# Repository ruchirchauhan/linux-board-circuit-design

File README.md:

# Custom SAM9X60 Embedded Linux Development Board

A custom-designed embedded development board based on the **Microchip SAM9X60** ARM926EJ-S microprocessor, designed to explore embedded Linux, hardware design, and low-level software development.

The project started with the goal of designing a minimal, fully functional Linux-capable board using the SAM9X60, taking inspiration from Microchip's SAM9X60 Curiosity evaluation board.

## Software Repository

The Operating System and board-bringup related documentation are maintained separately:

**[Linux Board OS](https://github.com/ruchirchauhan/linux-board-os)**

## Board Images

### 3D PCB Render

### Actual PCB

## Hardware Overview

| Component | Description |
|---|---|
| Processor | Microchip SAM9X60D1G-I/4FB |
| Power Management | Microchip MCP16501 PMIC |
| Ethernet PHY | Microchip KSZ8081RNAIA-TR |
| Ethernet Interface | 10/100 Mbps RMII |
| Storage | MicroSD card |
| Debug Interface | UART via USB-to-serial adapter |
| Power Input | 5V USB |

## Software Repository

The corresponding software repository contains the bootloader, Linux kernel configuration, device tree, and Buildroot configuration used to bring up and run embedded Linux on this board.

TODO
<!-- TODO **Software repository:** [SAM9X60 Linux Software](https://github.com/TODO) -->

## Software

The board has been successfully brought up with:

- U-Boot bootloader
- Microchip Linux4SAM kernel
- Buildroot-based embedded Linux filesystem

## Current Status

**Hardware bring-up completed successfully.**

All onboard peripherals are operational, including:

- Ethernet connectivity
- UART console
- MicroSD storage
- USB interfaces

The board successfully boots embedded Linux from microSD and provides a functional platform for further embedded software development and experimentation.

## Repository Contents

This repository contains the hardware design files for the custom SAM9X60 development board, including PCB layout and associated design resources.

## Project Goals

- Explore custom embedded hardware design.
- Gain hands-on experience with ARM-based embedded Linux platforms.
- Experiment with bootloaders, Linux kernel configuration, and device drivers.
- Develop and test embedded applications on custom hardware.

## Acknowledgments

The hardware design was developed with reference to Microchip's SAM9X60 Curiosity evaluation board documentation and reference design.

- [Microchip SAM9X60 Product Page](https://www.microchip.com/en-us/product/sam9x60)
- [Microchip Linux4SAM](https://www.linux4sam.org/)

---

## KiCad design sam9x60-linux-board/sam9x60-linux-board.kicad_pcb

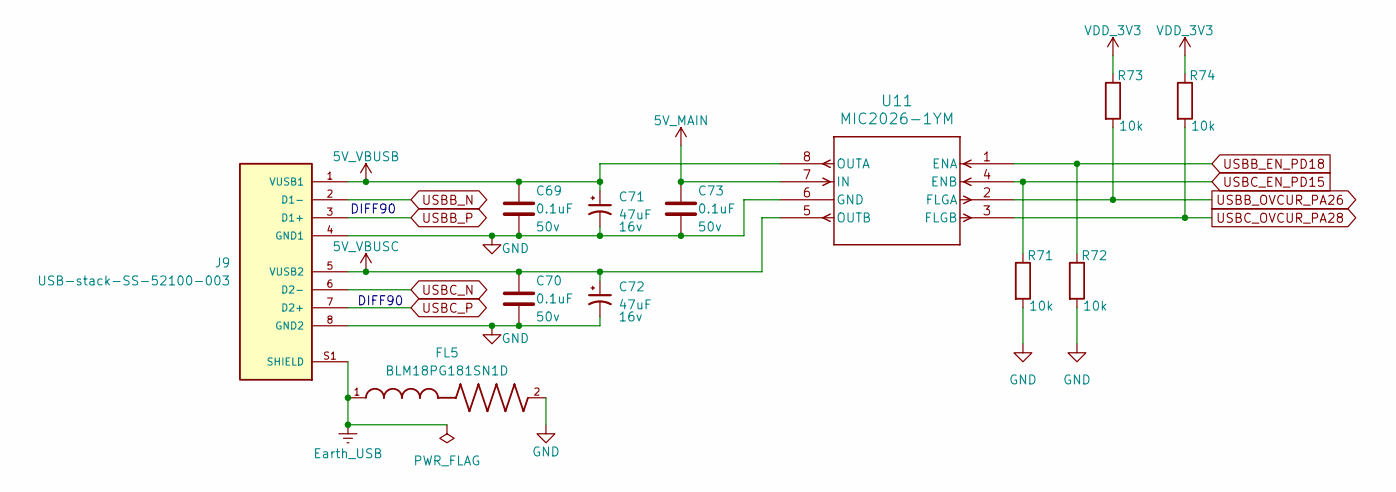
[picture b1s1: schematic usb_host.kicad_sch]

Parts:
C69, C70, C73: 0.1uF; C_0402_1005Metric_Pad0.74x0.62mm_HandSolder; Voltage 50v
C71, C72: 47uF; CP_Elec_5x5.4; Voltage 16v
FL5: BLM18PG181SN1D; BEADC1608X95N
J9: USB-stack-SS-52100-003; stacked-usb-BEL_SS-52100-003; PARTREV A0
R71, R72, R73, R74: 10k; R_0603_1608Metric
U11: MIC2026-1YM; mic2026-1ym-SOIC-8_M_MCL

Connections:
5V_MAIN: C73.1, U11.7 (IN); also elsewhere on the board
5V_VBUSB: C69.1, C71.1, J9.1 (VUSB1), U11.8 (OUTA)
5V_VBUSC: C70.1, C72.1, J9.5 (VUSB2), U11.5 (OUTB)
Earth_USB: FL5.1, J9.S1 (SHIELD), J9.S2 (SHIELD), J9.S3 (SHIELD), J9.S4 (SHIELD)
GND: C69.2, C70.2, C71.2, C72.2, C73.2, FL5.2, J9.4 (GND1), J9.8 (GND2), R71.2, R72.2, U11.6 (GND); also elsewhere on the board
USBB_EN_PD18: R72.1, U11.1 (ENA); also elsewhere on the board
USBB_N: J9.2 (D1-); also elsewhere on the board
USBB_OVCUR_PA26: R73.2, U11.2 (FLGA); also elsewhere on the board
USBB_P: J9.3 (D1+); also elsewhere on the board
USBC_EN_PD15: R71.1, U11.4 (ENB); also elsewhere on the board
USBC_N: J9.6 (D2-); also elsewhere on the board
USBC_OVCUR_PA28: R74.2, U11.3 (FLGB); also elsewhere on the board
USBC_P: J9.7 (D2+); also elsewhere on the board
VDD_3V3: R73.1, R74.1; also elsewhere on the board

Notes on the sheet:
DIFF90

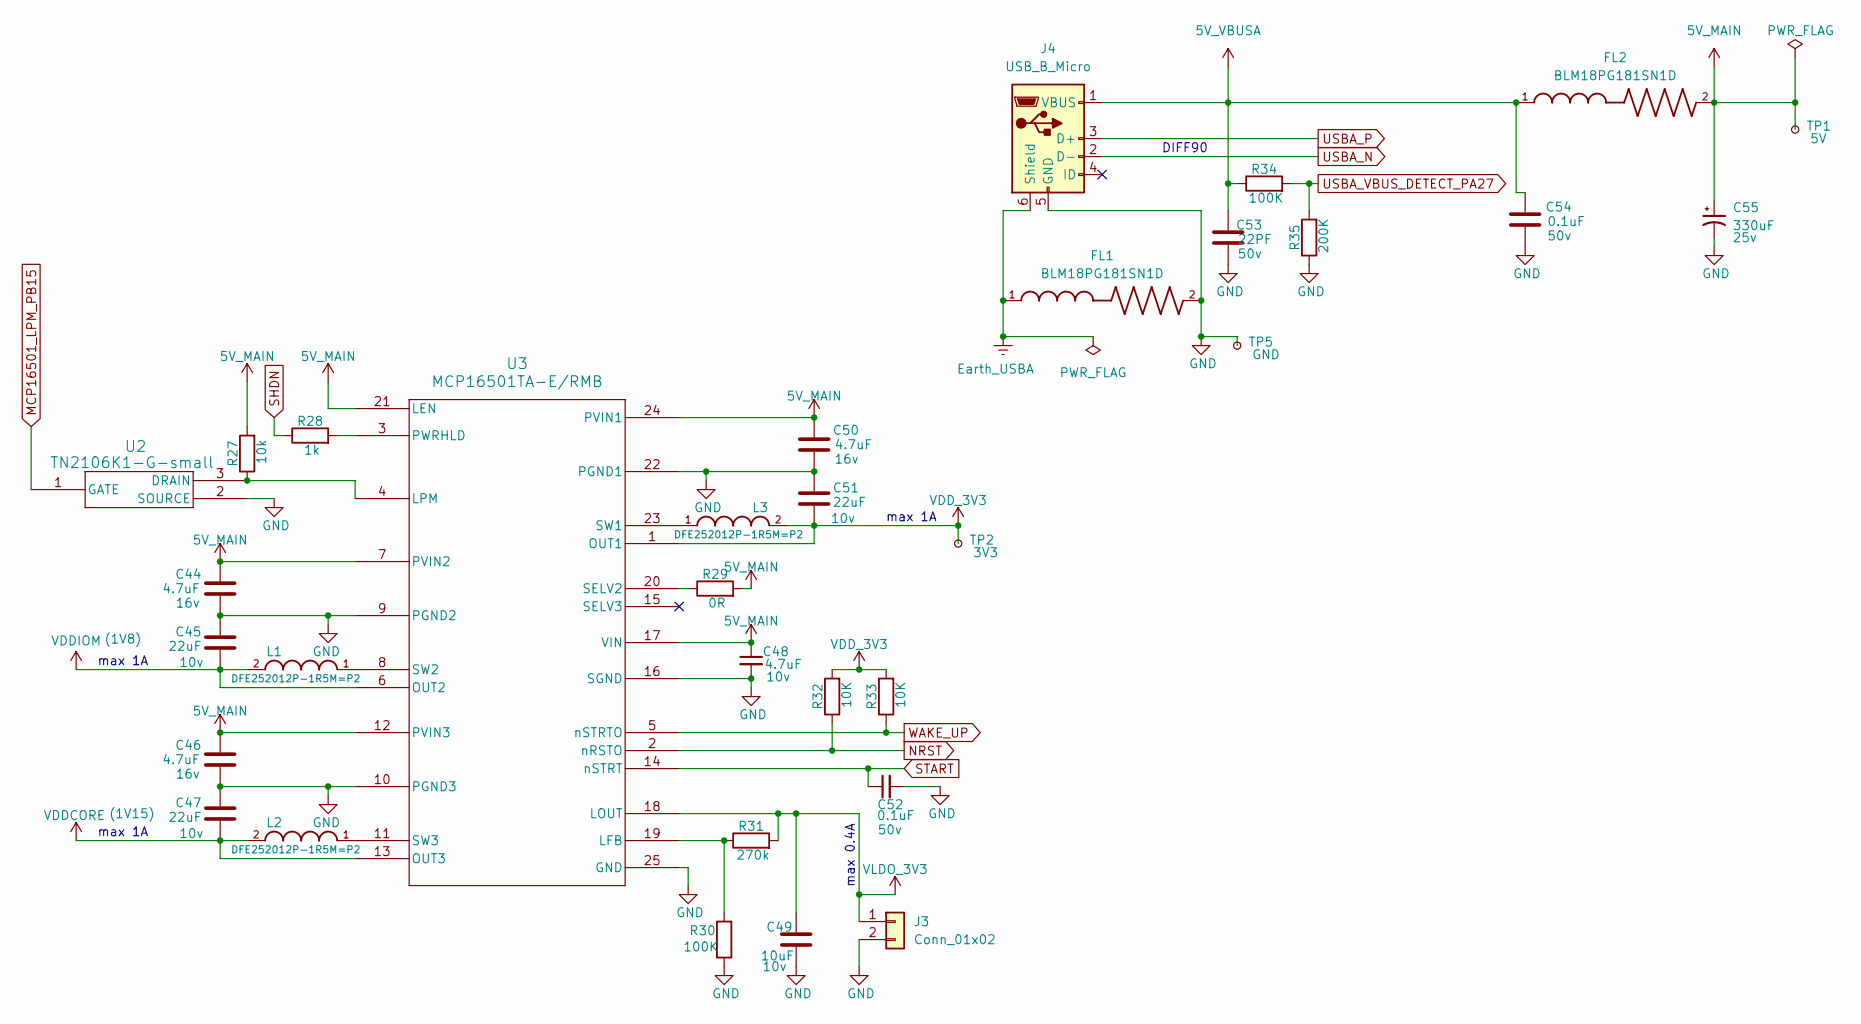
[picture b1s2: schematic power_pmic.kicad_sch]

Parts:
C44, C46, C50: 4.7uF; C_0805_2012Metric; Voltage 16v
C45, C47, C51: 22uF; C_0805_2012Metric; Voltage 10v
C48: 4.7uF; C_0805_2012Metric; Voltage 10v
C49: 10uF; C_0805_2012Metric; Voltage 10v
C52, C54: 0.1uF; C_0402_1005Metric_Pad0.74x0.62mm_HandSolder; Voltage 50v
C53: 22PF; C_0805_2012Metric; Voltage 50v
C55: 330uF; CP_Elec_10x10; Voltage 25v
FL1, FL2: BLM18PG181SN1D; BEADC1608X95N
J3: Conn_01x02; PinHeader_1x02_P2.54mm_Vertical
J4: USB_B_Micro; USB_Micro-B_Amphenol_10103594-0001LF_Horizontal
L1, L2, L3: DFE252012P-1R5M=P2; INDC2520X120N
R27: 10k; R_0603_1608Metric
R28: 1k; R_0603_1608Metric
R29: 0R; R_0603_1608Metric
R30, R34: 100K; R_0603_1608Metric
R31: 270k; R_0603_1608Metric
R32, R33: 10K; R_0603_1608Metric
R35: 200K; R_0603_1608Metric
TP1: 5V; TestPoint_THTPad_D2.0mm_Drill1.0mm
TP2: 3V3; TestPoint_THTPad_D2.0mm_Drill1.0mm
TP5: GND; TestPoint_THTPad_D2.0mm_Drill1.0mm
U2: TN2106K1-G-small; TO-236AB_MCH
U3: MCP16501TA-E/RMB; VQFN24_RMB_MCH

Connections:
5V_MAIN: C44.1, C46.1, C48.1, C50.1, C55.1, FL2.2, R27.2, R29.2, TP1.1, U3.7 (PVIN2), U3.12 (PVIN3), U3.17 (VIN), U3.21 (LEN), U3.24 (PVIN1); also elsewhere on the board
5V_VBUSA: C53.1, C54.1, FL2.1, J4.1 (VBUS), R34.1
Earth_USBA: FL1.1, J4.6 (Shield)
GND: C44.2, C45.1, C46.2, C47.1, C48.2, C49.2, C50.2, C51.1, C52.2, C53.2, C54.2, C55.2, FL1.2, J3.2, J4.5 (GND), R30.1, R35.1, TP5.1, U2.2 (SOURCE), U3.9 (PGND2), U3.10 (PGND3), U3.16 (SGND), U3.22 (PGND1), U3.25 (GND); also elsewhere on the board
MCP16501_LPM_PB15: U2.1 (GATE); also elsewhere on the board
NRST: R32.1, U3.2 (nRSTO); also elsewhere on the board
unnamed: R27.1, U2.3 (DRAIN), U3.4 (LPM)
unnamed: R30.2, R31.1, U3.19 (LFB)
unnamed: R28.2, U3.3 (PWRHLD)
unnamed: R29.1, U3.20 (SELV2)
unnamed: L3.1, U3.23 (SW1)
unnamed: L1.1, U3.8 (SW2)
unnamed: L2.1, U3.11 (SW3)
SHDN: R28.1; also elsewhere on the board
START: C52.1, U3.14 (nSTRT); also elsewhere on the board
USBA_N: J4.2 (D-); also elsewhere on the board
USBA_P: J4.3 (D+); also elsewhere on the board
USBA_VBUS_DETECT_PA27: R34.2, R35.2; also elsewhere on the board
VDDCORE: C47.2, L2.2, U3.13 (OUT3); also elsewhere on the board
VDDIOM: C45.2, L1.2, U3.6 (OUT2); also elsewhere on the board
VDD_3V3: C51.2, L3.2, R32.2, R33.2, TP2.1, U3.1 (OUT1); also elsewhere on the board
VLDO_3V3: C49.1, J3.1, R31.2, U3.18 (LOUT)
WAKE_UP: R33.1, U3.5 (nSTRTO); also elsewhere on the board

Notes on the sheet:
max 1A
DIFF90
max 0.4A

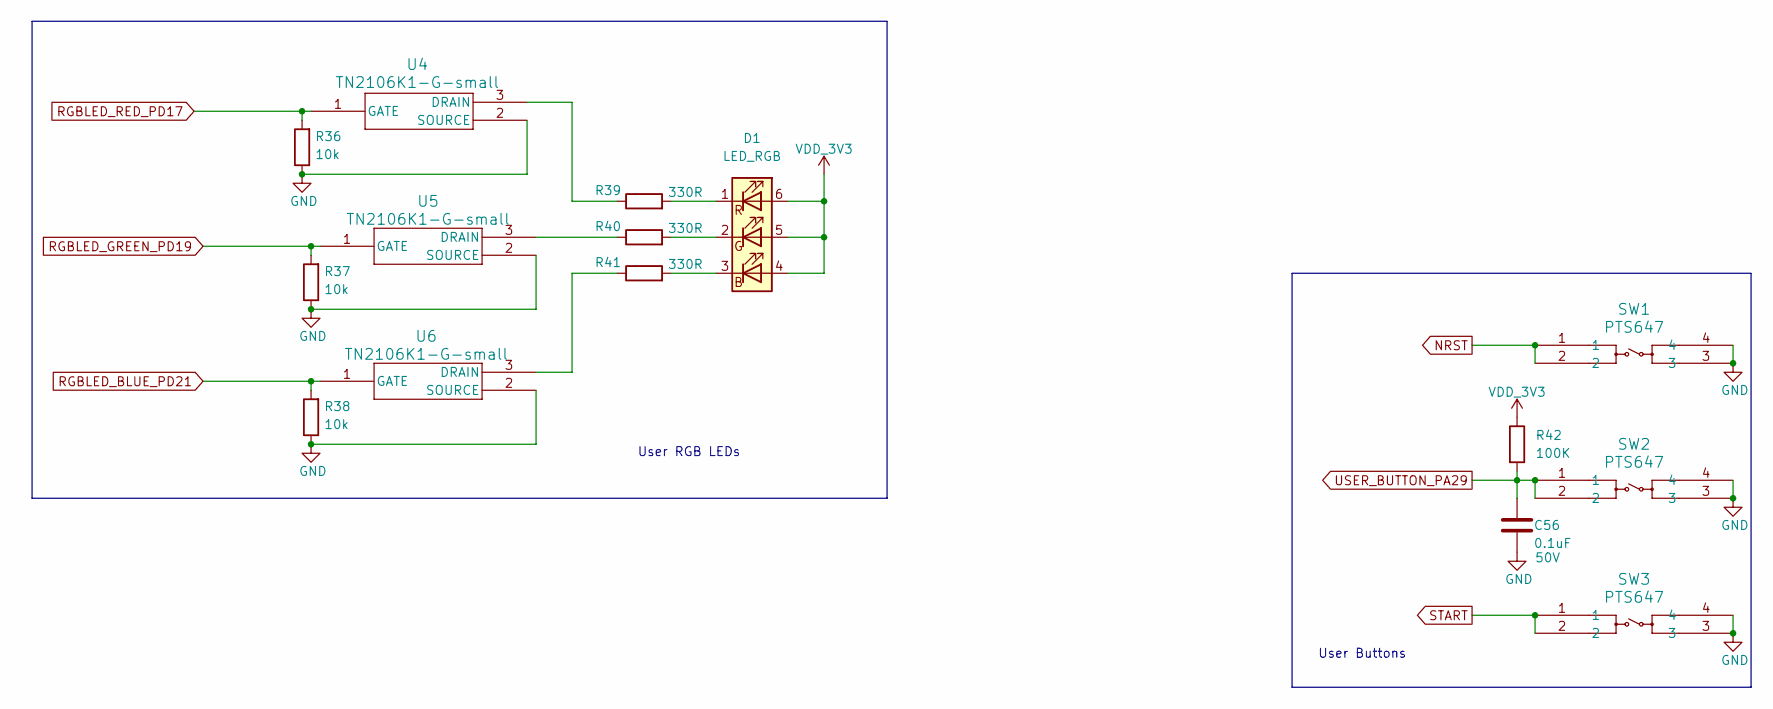
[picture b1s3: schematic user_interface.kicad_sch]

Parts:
C56: 0.1uF; C_0402_1005Metric_Pad0.74x0.62mm_HandSolder; Voltage 50V
D1: LED_RGB; LED_RGB_5050-6
R36, R37, R38: 10k; R_0603_1608Metric
R39, R40, R41: 330R; R_0603_1608Metric
R42: 100K; R_0603_1608Metric
SW1, SW2, SW3: PTS647; PTS 647 SN50 SMTR2 LFS
U4, U5, U6: TN2106K1-G-small; TO-236AB_MCH

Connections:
GND: C56.2, R36.1, R37.1, R38.1, SW1.3, SW1.4, SW2.3, SW2.4, SW3.3, SW3.4, U4.2 (SOURCE), U5.2 (SOURCE), U6.2 (SOURCE); also elsewhere on the board
NRST: SW1.1, SW1.2; also elsewhere on the board
unnamed: D1.3 (BK), R41.2
unnamed: D1.2 (GK), R40.2
unnamed: D1.1 (RK), R39.2
unnamed: R39.1, U4.3 (DRAIN)
unnamed: R40.1, U5.3 (DRAIN)
unnamed: R41.1, U6.3 (DRAIN)
RGBLED_BLUE_PD21: R38.2, U6.1 (GATE); also elsewhere on the board
RGBLED_GREEN_PD19: R37.2, U5.1 (GATE); also elsewhere on the board
RGBLED_RED_PD17: R36.2, U4.1 (GATE); also elsewhere on the board
START: SW3.1, SW3.2; also elsewhere on the board
USER_BUTTON_PA29: C56.1, R42.2, SW2.1, SW2.2; also elsewhere on the board
VDD_3V3: D1.4 (BA), D1.5 (GA), D1.6 (RA), R42.1; also elsewhere on the board

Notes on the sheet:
User Buttons
User RGB LEDs

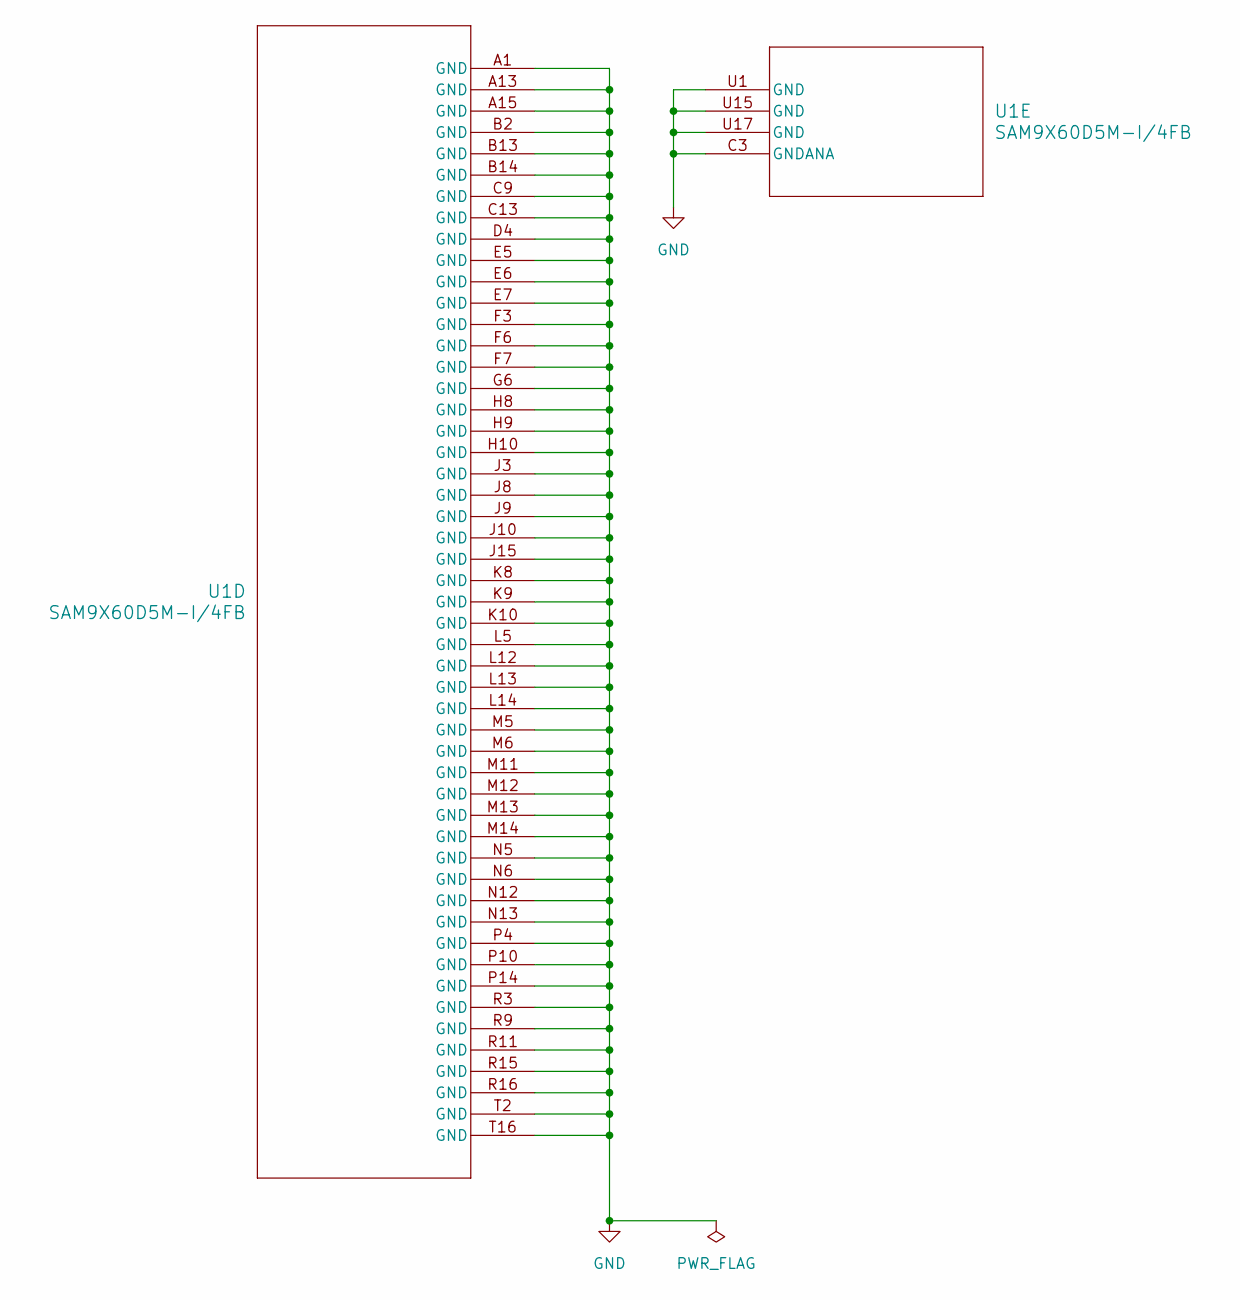
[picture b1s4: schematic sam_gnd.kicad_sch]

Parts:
U1: SAM9X60D5M-I/4FB; TFBGA233_4FB_MCH

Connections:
/sam_a_b_plus/DDRCAL: U1.C8 (DDR_CAL); also elsewhere on the board
/sam_a_b_plus/XIN24M: U1.T11 (XIN); also elsewhere on the board
/sam_a_b_plus/XIN32K: U1.U10 (XIN32); also elsewhere on the board
/sam_a_b_plus/XOUT24M: U1.U11 (XOUT); also elsewhere on the board
/sam_a_b_plus/XOUT32K: U1.T10 (XOUT32); also elsewhere on the board
DBGU_RX_PA9: U1.N2 (PA9); also elsewhere on the board
DBGU_TX_PA10: U1.M4 (PA10); also elsewhere on the board
EEPROM_TWCK_PA1: U1.L3 (PA1); also elsewhere on the board
EEPROM_TWD_PA0: U1.L2 (PA0); also elsewhere on the board
ETH0_IRQ_PB8: U1.D5 (PB8); also elsewhere on the board
ETH0_MDC_PB6: U1.D3 (PB6); also elsewhere on the board
ETH0_MDIO_PB5: U1.E1 (PB5); also elsewhere on the board
ETH0_NRST_PB16: U1.E2 (PB16); also elsewhere on the board
ETH0_RX0_PB0: U1.B3 (PB0); also elsewhere on the board
ETH0_RX1_PB1: U1.D1 (PB1); also elsewhere on the board
ETH0_RXDV_PB3: U1.D2 (PB3); also elsewhere on the board
ETH0_RXER_PB2: U1.A3 (PB2); also elsewhere on the board
ETH0_TX0_PB9: U1.B4 (PB9); also elsewhere on the board
ETH0_TX1_PB10: U1.B5 (PB10); also elsewhere on the board
ETH0_TXCK_PB4: U1.E3 (PB4); also elsewhere on the board
ETH0_TXEN_PB7: U1.F4 (PB7); also elsewhere on the board
FCOM1_UART_RX_PA6: U1.N1 (PA6); also elsewhere on the board
FCOM1_UART_TX_PA5: U1.N3 (PA5); also elsewhere on the board
FCOM5_SPI_CK_PA23: U1.C11 (PA23); also elsewhere on the board
FCOM5_SPI_MISO_PA21: U1.B11 (PA21); also elsewhere on the board
FCOM5_SPI_MOSI_PA22: U1.A10 (PA22); also elsewhere on the board
FCOM5_SPI_NPCS0_PA8: U1.P3 (PA8); also elsewhere on the board
FCOM5_SPI_NPCS1_PA7: U1.P2 (PA7); also elsewhere on the board
FCOM5_SPI_NPCS2_PA31: U1.H2 (PA31); also elsewhere on the board
FCOM5_SPI_NPCS3_PA30: U1.H1 (PA30); also elsewhere on the board
FCOM12_I2C_TWCK_PB22: U1.B8 (PB22); also elsewhere on the board
FCOM12_I2C_TWD_PB21: U1.A8 (PB21); also elsewhere on the board
GND: U1.A1 (GND), U1.A13 (GND), U1.A15 (GND), U1.B2 (GND), U1.B13 (GND), U1.B14 (GND), U1.C3 (GNDANA), U1.C9 (GND), U1.C13 (GND), U1.D4 (GND), U1.E5 (GND), U1.E6 (GND), U1.E7 (GND), U1.F3 (GND), U1.F6 (GND), U1.F7 (GND), U1.G6 (GND), U1.H8 (GND), U1.H9 (GND), U1.H10 (GND), U1.J3 (GND), U1.J8 (GND), U1.J9 (GND), U1.J10 (GND), U1.J15 (GND), U1.K8 (GND), U1.K9 (GND), U1.K10 (GND), U1.L5 (GND), U1.L12 (GND), U1.L13 (GND), U1.L14 (GND), U1.M5 (GND), U1.M6 (GND), U1.M11 (GND), U1.M12 (GND), U1.M13 (GND), U1.M14 (GND), U1.N5 (GND), U1.N6 (GND), U1.N7 (GNDIN33), U1.N12 (GND), U1.N13 (GND), U1.P4 (GND), U1.P7 (GNDIN33), U1.P10 (GND), U1.P14 (GND), U1.R3 (GND), U1.R9 (GND), U1.R11 (GND), U1.R15 (GND), U1.R16 (GND), U1.T2 (GND), U1.T16 (GND), U1.U1 (GND), U1.U15 (GND), U1.U17 (GND); also elsewhere on the board
MCP16501_LPM_PB15: U1.C4 (PB15); also elsewhere on the board
MPU_NRSTOUT_PB25: U1.B7 (PB25); also elsewhere on the board
NRST: U1.P1 (NRST); also elsewhere on the board
unnamed 76: U1.P11 (VDDOUT25); also elsewhere on the board
RTCK: U1.N4 (RTCK); also elsewhere on the board
SDMMC0_CD_PA25: U1.A9 (PA25); also elsewhere on the board
SDMMC0_CK_PA17: U1.H4 (PA17); also elsewhere on the board
SDMMC0_CMD_PA16: U1.J2 (PA16); also elsewhere on the board
SDMMC0_DAT0_PA15: U1.K1 (PA15); also elsewhere on the board
SDMMC0_DAT1_PA18: U1.H3 (PA18); also elsewhere on the board
SDMMC0_DAT2_PA19: U1.J1 (PA19); also elsewhere on the board
SDMMC0_DAT3_PA20: U1.J4 (PA20); also elsewhere on the board
SHDN: U1.N17 (SHDN); also elsewhere on the board
TCK: U1.P12 (TCK); also elsewhere on the board
TDI: U1.L15 (TDI); also elsewhere on the board
TDO: U1.N15 (TDO); also elsewhere on the board
TMS: U1.N16 (TMS); also elsewhere on the board
USBA_N: U1.U16 (HSDMA); also elsewhere on the board
USBA_P: U1.T15 (HSDPA); also elsewhere on the board
USBA_VBUS_DETECT_PA27: U1.D12 (PA27); also elsewhere on the board
USBB_N: U1.R17 (HSDMB); also elsewhere on the board
USBB_OVCUR_PA26: U1.D10 (PA26); also elsewhere on the board
USBB_P: U1.T17 (HSDPB); also elsewhere on the board
USBC_N: U1.P15 (HSDMC); also elsewhere on the board
USBC_OVCUR_PA28: U1.A11 (PA28); also elsewhere on the board
USBC_P: U1.P16 (HSDPC); also elsewhere on the board
USER_BUTTON_PA29: U1.C10 (PA29); also elsewhere on the board
VDD_3V3: U1.N11 (VDDIN33), U1.R12 (VDDIN33); also elsewhere on the board
WAKE_UP: U1.L16 (WKUP0); also elsewhere on the board

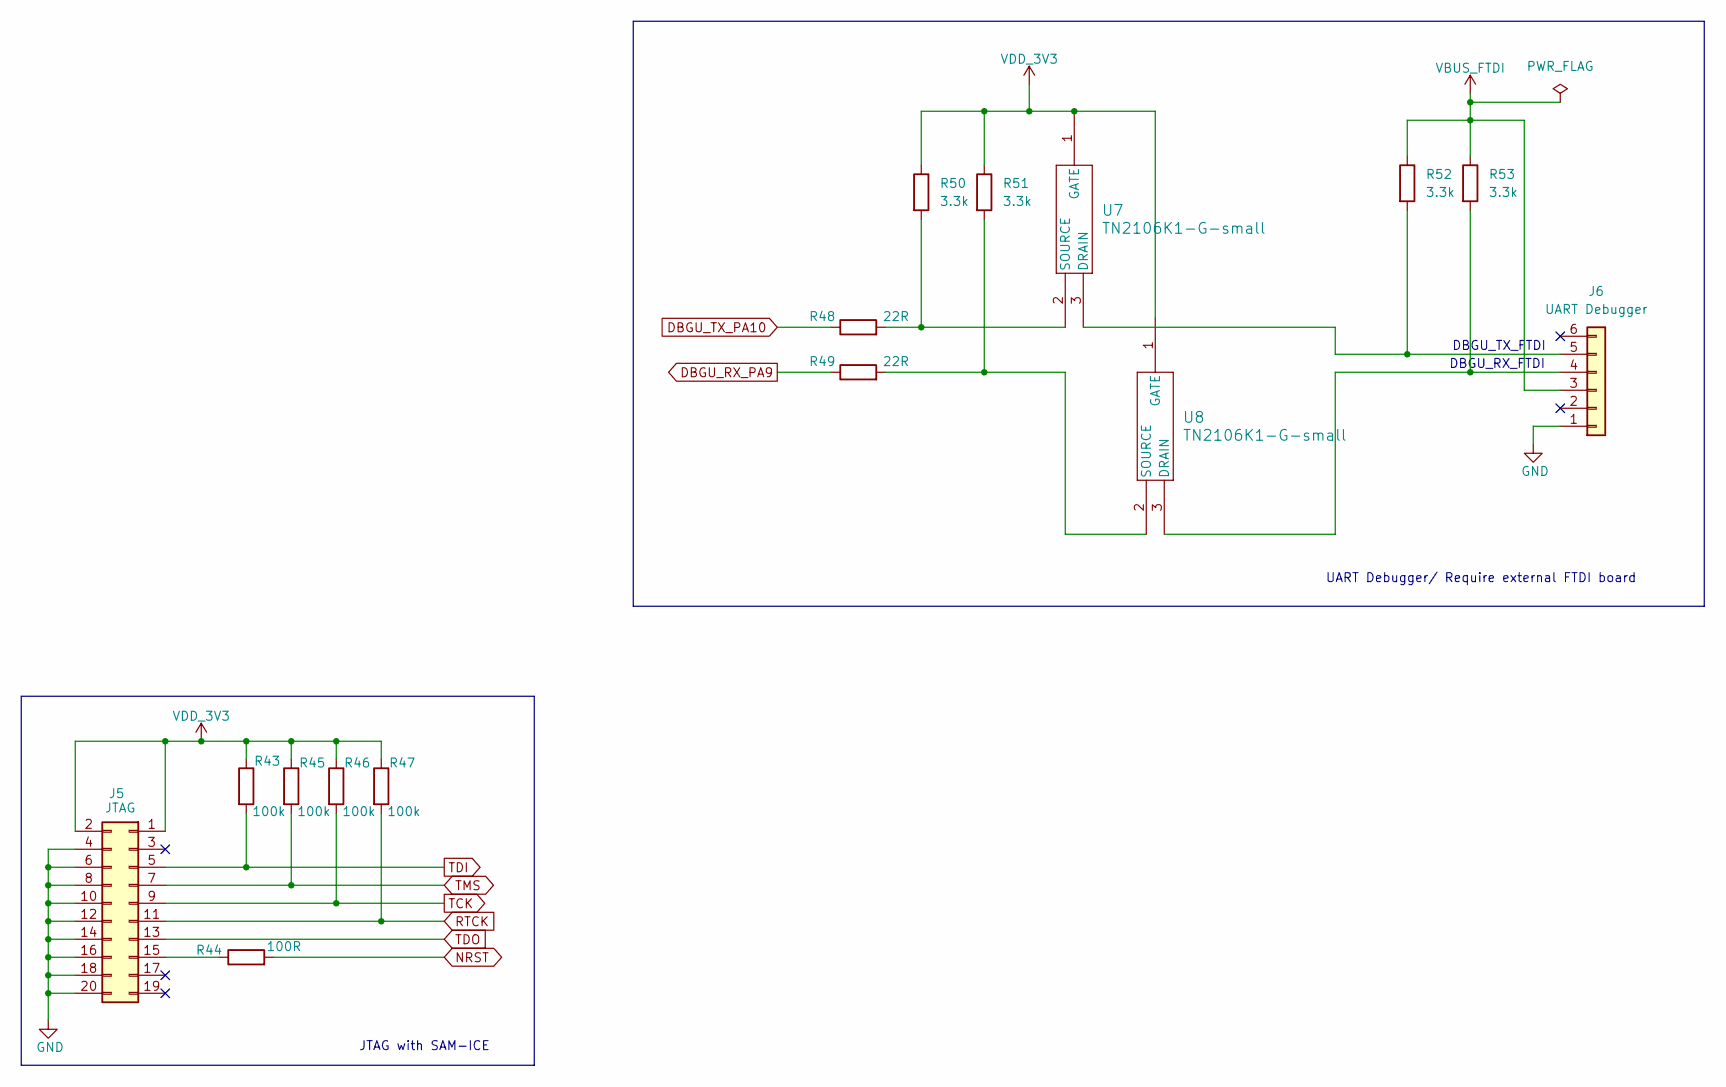
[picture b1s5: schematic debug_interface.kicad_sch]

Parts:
J5: JTAG; PinHeader_2x10_P2.54mm_Vertical
J6: UART Debugger; PinHeader_1x06_P2.54mm_Vertical
R43, R45, R46, R47: 100k; R_0603_1608Metric
R44: 100R; R_0603_1608Metric
R48, R49: 22R; R_0603_1608Metric
R50, R51, R52, R53: 3.3k; R_0603_1608Metric
U7, U8: TN2106K1-G-small; TO-236AB_MCH

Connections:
DBGU_RX_PA9: R49.1; also elsewhere on the board
DBGU_TX_PA10: R48.1; also elsewhere on the board
GND: J5.4, J5.6, J5.8, J5.10, J5.12, J5.14, J5.16, J5.18, J5.20, J6.1; also elsewhere on the board
NRST: R44.2; also elsewhere on the board
unnamed: J5.15, R44.1
unnamed: J6.4, R53.2, U8.3 (DRAIN)
unnamed: J6.5, R52.2, U7.3 (DRAIN)
unnamed: R48.2, R50.2, U7.2 (SOURCE)
unnamed: R49.2, R51.2, U8.2 (SOURCE)
RTCK: J5.11, R47.2; also elsewhere on the board
TCK: J5.9, R46.2; also elsewhere on the board
TDI: J5.5, R43.2; also elsewhere on the board
TDO: J5.13; also elsewhere on the board
TMS: J5.7, R45.2; also elsewhere on the board
VBUS_FTDI: J6.3, R52.1, R53.1
VDD_3V3: J5.1, J5.2, R43.1, R45.1, R46.1, R47.1, R50.1, R51.1, U7.1 (GATE), U8.1 (GATE); also elsewhere on the board

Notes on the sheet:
JTAG with SAM-ICE
DBGU_RX_FTDI
DBGU_TX_FTDI
UART Debugger/ Require external FTDI board

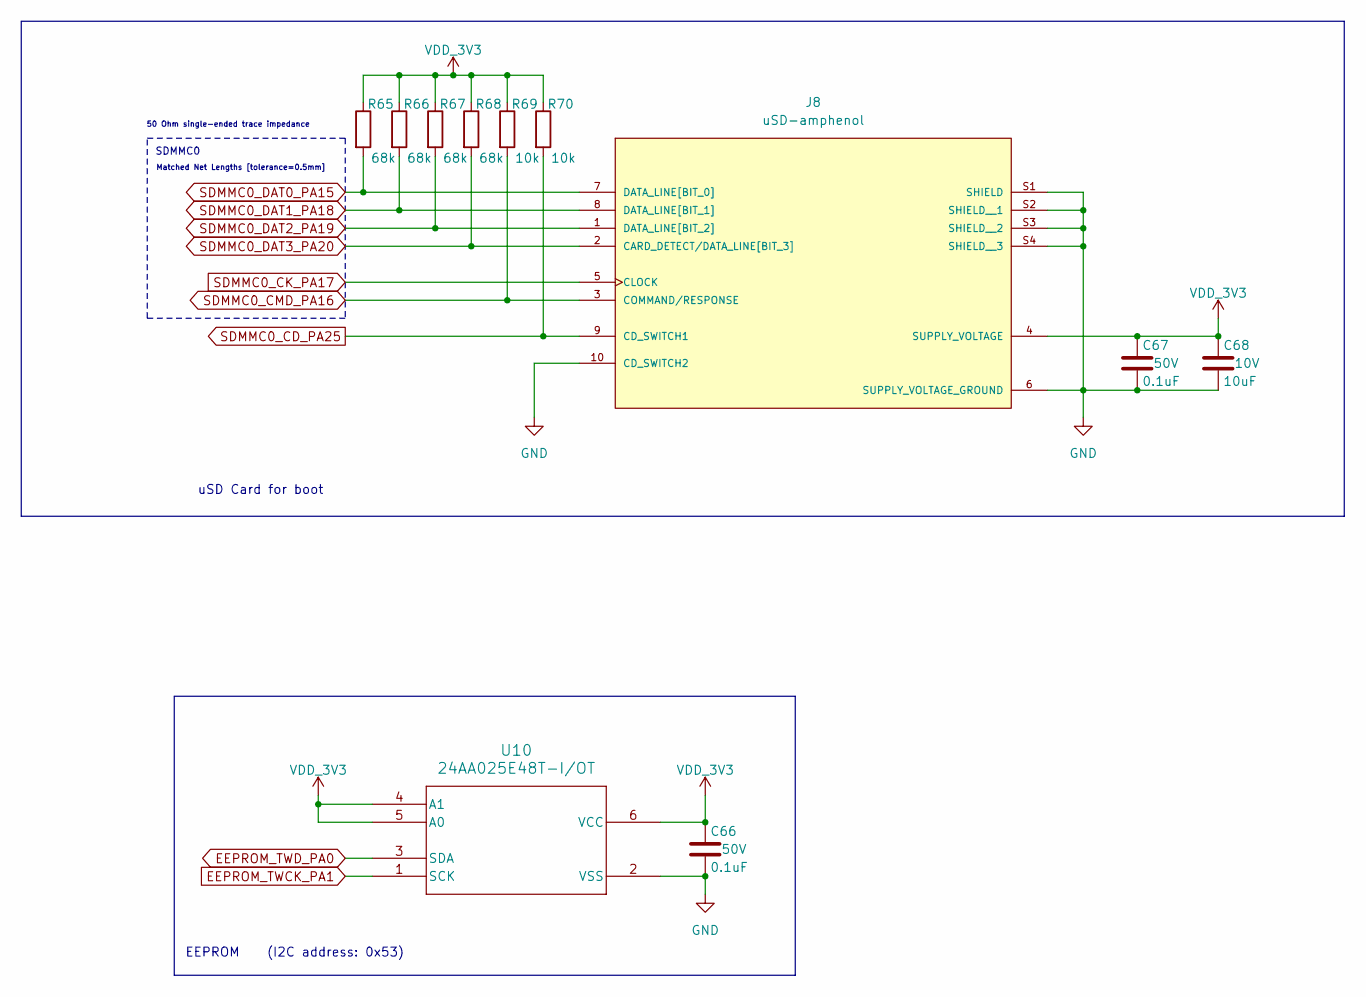
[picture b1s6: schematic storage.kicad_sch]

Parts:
C66, C67: 0.1uF; C_0402_1005Metric_Pad0.74x0.62mm_HandSolder; Voltage 50V
C68: 10uF; C_0805_2012Metric; Voltage 10V
J8: uSD-amphenol; AMPHENOL_1140084168; PARTREV A
R65, R66, R67, R68: 68k; R_0603_1608Metric
R69, R70: 10k; R_0603_1608Metric
U10: 24AA025E48T-I/OT; eeprom-SOT-23-6_MC_MCH

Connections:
EEPROM_TWCK_PA1: U10.1 (SCK); also elsewhere on the board
EEPROM_TWD_PA0: U10.3 (SDA); also elsewhere on the board
GND: C66.2, C67.2, C68.2, J8.6 (SUPPLY_VOLTAGE_GROUND), J8.10 (CD_SWITCH2), J8.S1 (SHIELD), J8.S2 (SHIELD__1), J8.S3 (SHIELD__2), J8.S4 (SHIELD__3), U10.2 (VSS); also elsewhere on the board
SDMMC0_CD_PA25: J8.9 (CD_SWITCH1), R70.2; also elsewhere on the board
SDMMC0_CK_PA17: J8.5 (CLOCK); also elsewhere on the board
SDMMC0_CMD_PA16: J8.3 (COMMAND/RESPONSE), R69.2; also elsewhere on the board
SDMMC0_DAT0_PA15: J8.7 (DATA_LINE[BIT_0]), R65.2; also elsewhere on the board
SDMMC0_DAT1_PA18: J8.8 (DATA_LINE[BIT_1]), R66.2; also elsewhere on the board
SDMMC0_DAT2_PA19: J8.1 (DATA_LINE[BIT_2]), R67.2; also elsewhere on the board
SDMMC0_DAT3_PA20: J8.2 (CARD_DETECT/DATA_LINE[BIT_3]), R68.2; also elsewhere on the board
VDD_3V3: C66.1, C67.1, C68.1, J8.4 (SUPPLY_VOLTAGE), R65.1, R66.1, R67.1, R68.1, R69.1, R70.1, U10.4 (A1), U10.5 (A0), U10.6 (VCC); also elsewhere on the board

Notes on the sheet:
50 Ohm single-ended trace impedance
uSD Card for boot
EEPROM (I2C address: 0x53)
SDMMC0
Matched Net Lengths [tolerance=0.5mm]

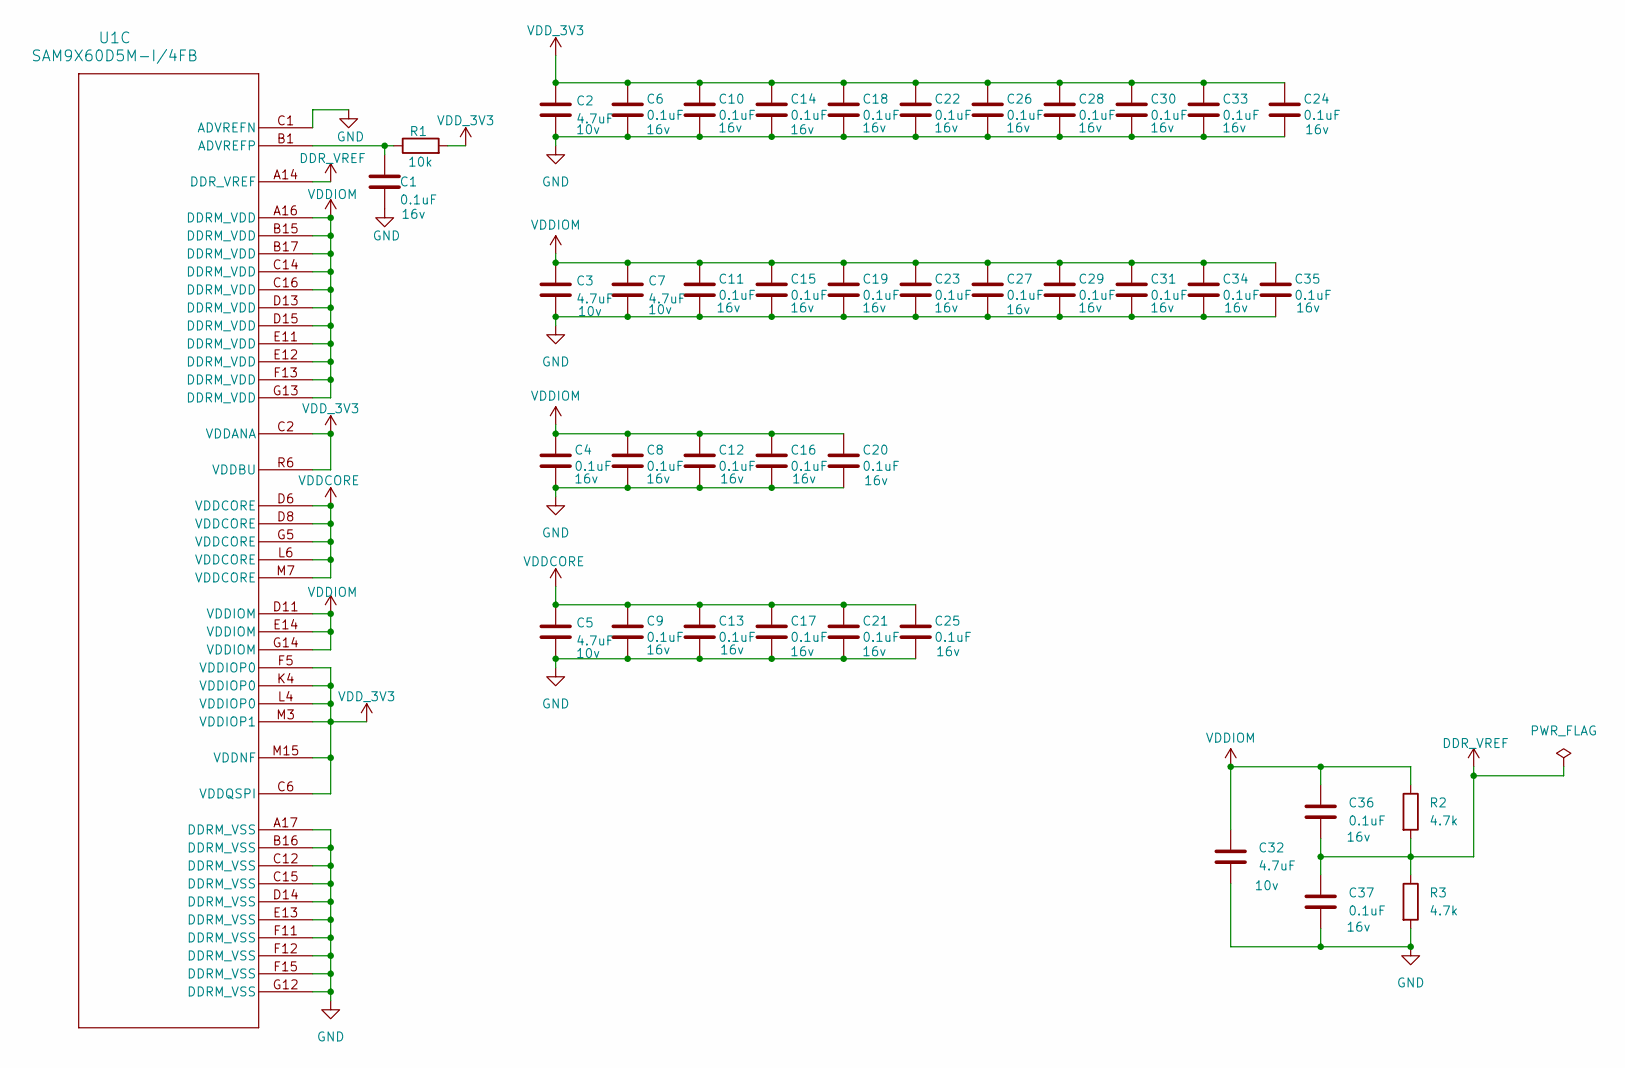
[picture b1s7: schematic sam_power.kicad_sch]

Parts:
C1, C4, C6, C8, C9, C10, C11, C12, C13, C14, C15, C16, C17, C18, C19, C20, C21, C22, C23, C24, C25, C26, C27, C28, C29, C30, C31, C33, C34, C35, C36, C37: 0.1uF; C_0402_1005Metric_Pad0.74x0.62mm_HandSolder; Voltage 16v
C2, C3, C5, C7, C32: 4.7uF; C_0805_2012Metric; Voltage 10v
R1: 10k; R_0603_1608Metric
R2, R3: 4.7k; R_0603_1608Metric
U1: SAM9X60D5M-I/4FB; TFBGA233_4FB_MCH

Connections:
/sam_a_b_plus/DDRCAL: U1.C8 (DDR_CAL); also elsewhere on the board
/sam_a_b_plus/XIN24M: U1.T11 (XIN); also elsewhere on the board
/sam_a_b_plus/XIN32K: U1.U10 (XIN32); also elsewhere on the board
/sam_a_b_plus/XOUT24M: U1.U11 (XOUT); also elsewhere on the board
/sam_a_b_plus/XOUT32K: U1.T10 (XOUT32); also elsewhere on the board
DBGU_RX_PA9: U1.N2 (PA9); also elsewhere on the board
DBGU_TX_PA10: U1.M4 (PA10); also elsewhere on the board
DDR_VREF: C36.2, C37.1, R2.2, R3.1, U1.A14 (DDR_VREF)
EEPROM_TWCK_PA1: U1.L3 (PA1); also elsewhere on the board
EEPROM_TWD_PA0: U1.L2 (PA0); also elsewhere on the board
ETH0_IRQ_PB8: U1.D5 (PB8); also elsewhere on the board
ETH0_MDC_PB6: U1.D3 (PB6); also elsewhere on the board
ETH0_MDIO_PB5: U1.E1 (PB5); also elsewhere on the board
ETH0_NRST_PB16: U1.E2 (PB16); also elsewhere on the board
ETH0_RX0_PB0: U1.B3 (PB0); also elsewhere on the board
ETH0_RX1_PB1: U1.D1 (PB1); also elsewhere on the board
ETH0_RXDV_PB3: U1.D2 (PB3); also elsewhere on the board
ETH0_RXER_PB2: U1.A3 (PB2); also elsewhere on the board
ETH0_TX0_PB9: U1.B4 (PB9); also elsewhere on the board
ETH0_TX1_PB10: U1.B5 (PB10); also elsewhere on the board
ETH0_TXCK_PB4: U1.E3 (PB4); also elsewhere on the board
ETH0_TXEN_PB7: U1.F4 (PB7); also elsewhere on the board
FCOM1_UART_RX_PA6: U1.N1 (PA6); also elsewhere on the board
FCOM1_UART_TX_PA5: U1.N3 (PA5); also elsewhere on the board
FCOM5_SPI_CK_PA23: U1.C11 (PA23); also elsewhere on the board
FCOM5_SPI_MISO_PA21: U1.B11 (PA21); also elsewhere on the board
FCOM5_SPI_MOSI_PA22: U1.A10 (PA22); also elsewhere on the board
FCOM5_SPI_NPCS0_PA8: U1.P3 (PA8); also elsewhere on the board
FCOM5_SPI_NPCS1_PA7: U1.P2 (PA7); also elsewhere on the board
FCOM5_SPI_NPCS2_PA31: U1.H2 (PA31); also elsewhere on the board
FCOM5_SPI_NPCS3_PA30: U1.H1 (PA30); also elsewhere on the board
FCOM12_I2C_TWCK_PB22: U1.B8 (PB22); also elsewhere on the board
FCOM12_I2C_TWD_PB21: U1.A8 (PB21); also elsewhere on the board
GND: C1.1, C2.2, C3.2, C4.2, C5.2, C6.2, C7.2, C8.2, C9.2, C10.2, C11.2, C12.2, C13.2, C14.2, C15.2, C16.2, C17.2, C18.2, C19.2, C20.2, C21.2, C22.2, C23.2, C24.2, C25.2, C26.2, C27.2, C28.2, C29.2, C30.2, C31.2, C32.2, C33.2, C34.2, C35.2, C37.2, R3.2, U1.A17 (DDRM_VSS), U1.B16 (DDRM_VSS), U1.C1 (ADVREFN), U1.C12 (DDRM_VSS), U1.C15 (DDRM_VSS), U1.D14 (DDRM_VSS), U1.E13 (DDRM_VSS), U1.F11 (DDRM_VSS), U1.F12 (DDRM_VSS), U1.F15 (DDRM_VSS), U1.G12 (DDRM_VSS), U1.N7 (GNDIN33), U1.P7 (GNDIN33); also elsewhere on the board
MCP16501_LPM_PB15: U1.C4 (PB15); also elsewhere on the board
MPU_NRSTOUT_PB25: U1.B7 (PB25); also elsewhere on the board
NRST: U1.P1 (NRST); also elsewhere on the board
unnamed 76: U1.P11 (VDDOUT25); also elsewhere on the board
unnamed: C1.2, R1.1, U1.B1 (ADVREFP)
RTCK: U1.N4 (RTCK); also elsewhere on the board
SDMMC0_CD_PA25: U1.A9 (PA25); also elsewhere on the board
SDMMC0_CK_PA17: U1.H4 (PA17); also elsewhere on the board
SDMMC0_CMD_PA16: U1.J2 (PA16); also elsewhere on the board
SDMMC0_DAT0_PA15: U1.K1 (PA15); also elsewhere on the board
SDMMC0_DAT1_PA18: U1.H3 (PA18); also elsewhere on the board
SDMMC0_DAT2_PA19: U1.J1 (PA19); also elsewhere on the board
SDMMC0_DAT3_PA20: U1.J4 (PA20); also elsewhere on the board
SHDN: U1.N17 (SHDN); also elsewhere on the board
TCK: U1.P12 (TCK); also elsewhere on the board
TDI: U1.L15 (TDI); also elsewhere on the board
TDO: U1.N15 (TDO); also elsewhere on the board
TMS: U1.N16 (TMS); also elsewhere on the board
USBA_N: U1.U16 (HSDMA); also elsewhere on the board
USBA_P: U1.T15 (HSDPA); also elsewhere on the board
USBA_VBUS_DETECT_PA27: U1.D12 (PA27); also elsewhere on the board
USBB_N: U1.R17 (HSDMB); also elsewhere on the board
USBB_OVCUR_PA26: U1.D10 (PA26); also elsewhere on the board
USBB_P: U1.T17 (HSDPB); also elsewhere on the board
USBC_N: U1.P15 (HSDMC); also elsewhere on the board
USBC_OVCUR_PA28: U1.A11 (PA28); also elsewhere on the board
USBC_P: U1.P16 (HSDPC); also elsewhere on the board
USER_BUTTON_PA29: U1.C10 (PA29); also elsewhere on the board
VDDCORE: C5.1, C9.1, C13.1, C17.1, C21.1, C25.1, U1.D6 (VDDCORE), U1.D8 (VDDCORE), U1.G5 (VDDCORE), U1.L6 (VDDCORE), U1.M7 (VDDCORE); also elsewhere on the board
VDDIOM: C3.1, C4.1, C7.1, C8.1, C11.1, C12.1, C15.1, C16.1, C19.1, C20.1, C23.1, C27.1, C29.1, C31.1, C32.1, C34.1, C35.1, C36.1, R2.1, U1.A16 (DDRM_VDD), U1.B15 (DDRM_VDD), U1.B17 (DDRM_VDD), U1.C14 (DDRM_VDD), U1.C16 (DDRM_VDD), U1.D11 (VDDIOM), U1.D13 (DDRM_VDD), U1.D15 (DDRM_VDD), U1.E11 (DDRM_VDD), U1.E12 (DDRM_VDD), U1.E14 (VDDIOM), U1.F13 (DDRM_VDD), U1.G13 (DDRM_VDD), U1.G14 (VDDIOM); also elsewhere on the board
VDD_3V3: C2.1, C6.1, C10.1, C14.1, C18.1, C22.1, C24.1, C26.1, C28.1, C30.1, C33.1, R1.2, U1.C2 (VDDANA), U1.C6 (VDDQSPI), U1.F5 (VDDIOP0), U1.K4 (VDDIOP0), U1.L4 (VDDIOP0), U1.M3 (VDDIOP1), U1.M15 (VDDNF), U1.N11 (VDDIN33), U1.R6 (VDDBU), U1.R12 (VDDIN33); also elsewhere on the board
WAKE_UP: U1.L16 (WKUP0); also elsewhere on the board
